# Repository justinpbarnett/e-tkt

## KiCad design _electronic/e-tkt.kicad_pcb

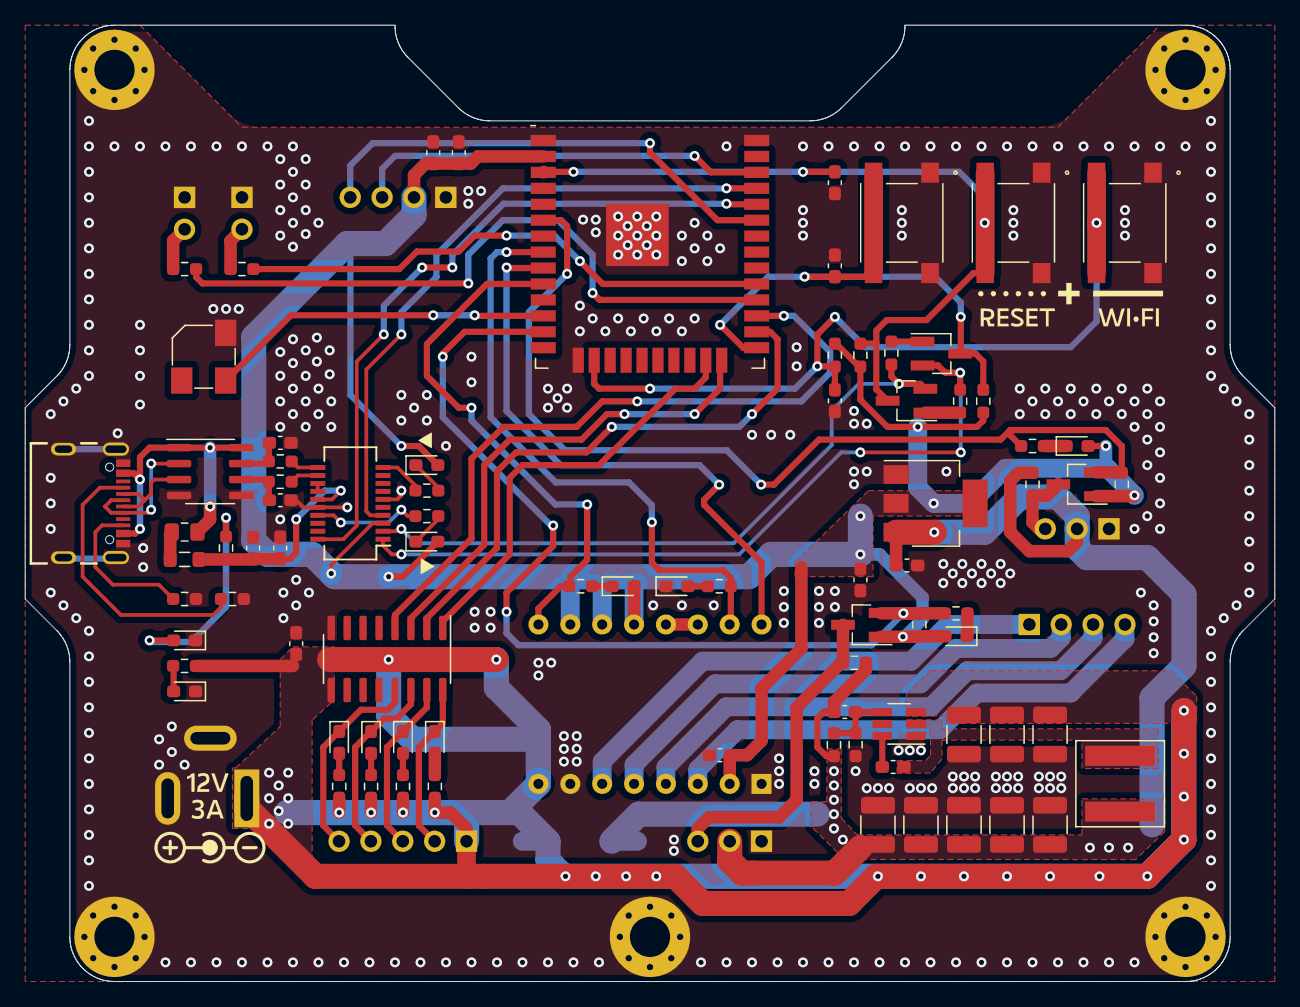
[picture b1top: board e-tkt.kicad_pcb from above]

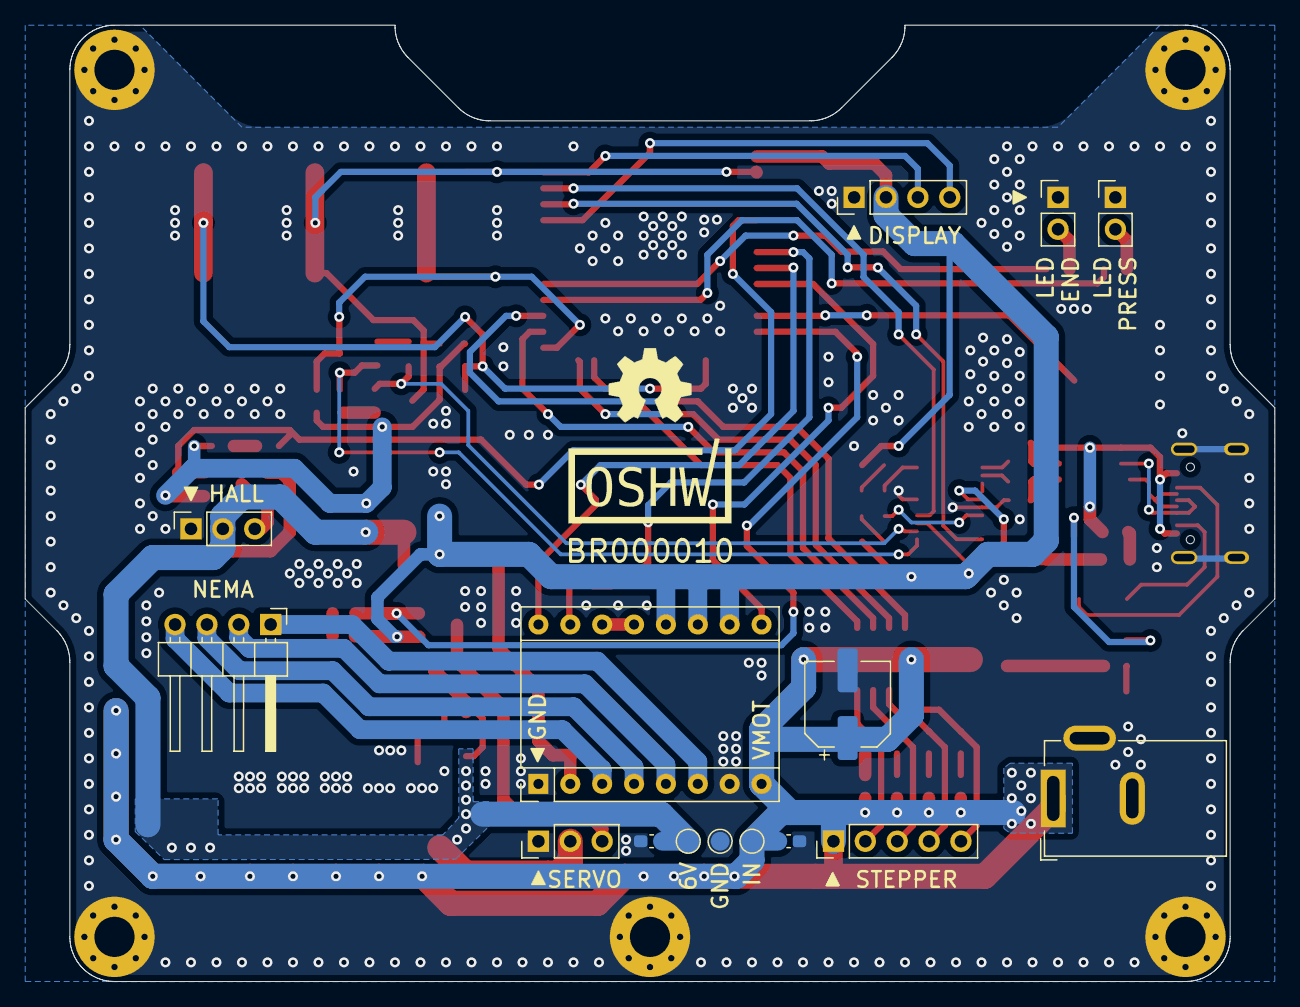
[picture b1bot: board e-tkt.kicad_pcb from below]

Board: 4 copper layers, 99.6 x 76.2 mm, 102 parts (15 on the bottom side), 69 nets.

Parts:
A_NEMA1: 8+8 pin; Pololu_Breakout-16_15.2x20.3mm
C_ENA1: 0.1uF 50V; C_0603_1608Metric_Pad1.08x0.95mm_HandSolder
C_MCU1: 0.1uF 50V; C_0603_1608Metric_Pad1.08x0.95mm_HandSolder
C_MCU2: 22uF 12V 1mOhm; C_0603_1608Metric_Pad1.08x0.95mm_HandSolder
C_NEMA1: 100uF 25V; CP_Elec_6.3x7.7
C_NEMA2: 10uF 12V 5mOhm; C_0603_1608Metric_Pad1.08x0.95mm_HandSolder
C_POW1: 10uF 12V 5mOhm; C_0603_1608Metric_Pad1.08x0.95mm_HandSolder
C_POW2: 22uF 12V 1mOhm; C_0603_1608Metric_Pad1.08x0.95mm_HandSolder
C_POW_6V_FF1: 82pF 100V; C_0603_1608Metric_Pad1.08x0.95mm_HandSolder
C_POW_BST1, C_POW_BST3: 0.1uF 50V; C_0603_1608Metric_Pad1.08x0.95mm_HandSolder
C_POW_BST2: 0.33uF 50V; C_0603_1608Metric_Pad1.08x0.95mm_HandSolder
C_POW_IN1, C_POW_IN2, C_POW_IN3: 10uF 25V; C_1210_3225Metric_Pad1.33x2.70mm_HandSolder
C_POW_OUT1, C_POW_OUT2, C_POW_OUT3, C_POW_OUT4, C_POW_OUT5: 22uF 25V; C_1210_3225Metric_Pad1.33x2.70mm_HandSolder
C_RST1: 0.1uF 50V; C_0603_1608Metric_Pad1.08x0.95mm_HandSolder
C_SER2, C_SER3: 47pF 5V; C_0603_1608Metric_Pad1.08x0.95mm_HandSolder
C_SER4: 0.1uF 50V; C_0603_1608Metric_Pad1.08x0.95mm_HandSolder
C_SER5: 10uF 12V 5mOhm; C_0603_1608Metric_Pad1.08x0.95mm_HandSolder
C_STP1: 10uF 12V 5mOhm; C_0603_1608Metric_Pad1.08x0.95mm_HandSolder
C_WIFI1: 0.1uF 50V; C_0603_1608Metric_Pad1.08x0.95mm_HandSolder
D_HALL1: LED white; LED_0603_1608Metric_Pad1.05x0.95mm_HandSolder
D_NEMA1, D_NEMA2: LED white; LED_0603_1608Metric_Pad1.05x0.95mm_HandSolder
D_POW2: LED white; LED_0603_1608Metric_Pad1.05x0.95mm_HandSolder
D_RX1: LED white; LED_0603_1608Metric_Pad1.05x0.95mm_HandSolder
D_SERVO1: LED white; LED_0603_1608Metric_Pad1.05x0.95mm_HandSolder
D_STP1, D_STP2, D_STP3, D_STP4: LED white; LED_0603_1608Metric_Pad1.05x0.95mm_HandSolder
D_TX1: LED white; LED_0603_1608Metric_Pad1.05x0.95mm_HandSolder
D_USB1: LED white; LED_0603_1608Metric_Pad1.05x0.95mm_HandSolder
FB_USB1: 40 Ohms @ 100 MHz 1 Power; L_0805_2012Metric_Pad1.05x1.20mm_HandSolder
F_USB1: 6V 750mA; Fuse_0805_2012Metric_Pad1.15x1.40mm_HandSolder
H1, H2, H3, H4, H6: M3; MountingHole_3.2mm_M3_Pad_Via
J_28byj-48-12v_1: Conn_01x05_Male; PinHeader_1x05_P2.54mm_Vertical
J_B_6v_1, J_B_12v_1: TestPoint; TestPoint_Pad_D1.5mm
J_B_GND_1: TestPoint; TestPoint_Pad_D1.5mm
J_HALL1: Conn_01x03_Female; PinSocket_1x03_P2.54mm_Vertical
J_LEDE1: Conn_01x02_Male; PinHeader_1x02_P2.54mm_Vertical
J_LEDP1: Conn_01x02_Male; PinHeader_1x02_P2.54mm_Vertical
J_NEMA1: Conn_01x04_Male; PinHeader_1x04_P2.54mm_Horizontal
J_OLED1: Conn_01x04_Male; PinHeader_1x04_P2.54mm_Vertical
J_POW1: Barrel_Jack_Switch; BarrelJack_GCT_DCJ200-10-A_Horizontal
J_SERVO1: Conn_01x03_Male; PinHeader_1x03_P2.54mm_Vertical
J_USB1: USB4105-GF-A; GCT_USB4105-GF-A
L1: SRP6060FA-100M; SRP6060FA-4R7M
LS1: CSS-0575A-SMT; CUI_CSS-0575A-SMT
Q_AUTO1, Q_AUTO2: SS8050; SOT-23_Handsoldering
Q_HALL1: BSS138LT3G; SOT-23_Handsoldering
Q_SERVO1: BSS138LT3G; SOT-23_Handsoldering
R_AUTO1, R_AUTO2: 10K (5%); R_0603_1608Metric_Pad0.98x0.95mm_HandSolder
R_ENA1: 10K (5%); R_0603_1608Metric_Pad0.98x0.95mm_HandSolder
R_HALL1, R_HALL2: 10K (5%); R_0603_1608Metric_Pad0.98x0.95mm_HandSolder
R_HALL3: 27R; R_0603_1608Metric_Pad0.98x0.95mm_HandSolder
R_LEDE1: 27R; R_0603_1608Metric_Pad0.98x0.95mm_HandSolder
R_LEDP1: 27R; R_0603_1608Metric_Pad0.98x0.95mm_HandSolder
R_NEMA1, R_NEMA2: 27R; R_0603_1608Metric_Pad0.98x0.95mm_HandSolder
R_POW6: 430R; R_0603_1608Metric_Pad0.98x0.95mm_HandSolder
R_POW_FBT1: 100K; R_0603_1608Metric_Pad0.98x0.95mm_HandSolder
R_POW_FFB1: 11K; R_0603_1608Metric_Pad0.98x0.95mm_HandSolder
R_RST1: 10K (5%); R_0603_1608Metric_Pad0.98x0.95mm_HandSolder
R_RX1: 27R; R_0603_1608Metric_Pad0.98x0.95mm_HandSolder
R_SER1, R_SER2: 27R; R_0603_1608Metric_Pad0.98x0.95mm_HandSolder
R_SERVO1, R_SERVO2: 10K (5%); R_0603_1608Metric_Pad0.98x0.95mm_HandSolder
R_SERVO3: 27R; R_0603_1608Metric_Pad0.98x0.95mm_HandSolder
R_STP1, R_STP2, R_STP3, R_STP4: 430R; R_0603_1608Metric_Pad0.98x0.95mm_HandSolder
R_TX1: 27R; R_0603_1608Metric_Pad0.98x0.95mm_HandSolder
R_USB1, R_USB2: 5.1K (10%); R_0603_1608Metric_Pad0.98x0.95mm_HandSolder
R_USB3: 100R; R_0603_1608Metric_Pad0.98x0.95mm_HandSolder
R_WIFI1: 10K(5%); R_0603_1608Metric_Pad0.98x0.95mm_HandSolder
SW_ENA1: B3FS-1000
SW_RST1: B3FS-1000
SW_WIFI1: B3FS-1000
U_MCU1: ESP32-WROOM-32
U_POW1: SOT-23-6_Handsoldering
U_POW2: AZ1117CH-3.3TRG1; SOT-223
U_SER1: FT231XS-R; SSOP-20_3.9x8.7mm_P0.635mm
U_STP1: ULN2003; SOIC-16_3.9x9.9mm_P1.27mm
U_USB1: USB6B1; SOIC-8_3.9x4.9mm_P1.27mm

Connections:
+3.3V: A_NEMA1.2 (VDD), A_NEMA1.10 (MS1), A_NEMA1.11 (MS2), A_NEMA1.12 (MS3), C_MCU1.1, C_MCU2.2, C_NEMA2.2, C_POW2.1, D_HALL1.2 (A), D_NEMA1.2 (A), D_RX1.2 (A), D_SERVO1.2 (A), D_TX1.2 (A), J_OLED1.2, Q_HALL1.1 (G), Q_SERVO1.1 (G), R_ENA1.2, R_HALL2.2, R_RST1.1, R_SERVO2.2, R_WIFI1.2, U_MCU1.2 (VDD), U_POW2.2 (OUT), U_POW2.4 (VOUT), U_SER1.3 (VCCIO)
+6V: C_POW1.1, C_POW_6V_FF1.1, C_POW_BST3.1, C_POW_OUT1.1, C_POW_OUT2.1, C_POW_OUT3.1, C_POW_OUT4.1, C_POW_OUT5.1, J_B_6v_1.1, J_HALL1.2, J_SERVO1.2, L1.2, R_HALL1.2, R_POW_FBT1.2, R_SERVO1.2, U_POW2.3 (IN)
+12V: A_NEMA1.8 (VMOT), C_NEMA1.1, C_POW_BST2.2, C_POW_IN1.1, C_POW_IN2.1, C_POW_IN3.1, C_STP1.2, J_28byj-48-12v_1.1, J_B_12v_1.1, J_POW1.1, R_POW6.1, R_STP1.1, R_STP2.1, R_STP3.1, R_STP4.1, U_POW1.3 (VIN), U_STP1.9 (COM)
/MCU/IO27 BUZZER OUT: LS1.1, U_MCU1.12 (IO27)
/USB-C 2.0/USBD1+: J_USB1.A6 (DP1), J_USB1.B6 (DP2), U_USB1.2 (I/O1)
/USB-C 2.0/USBD1-: J_USB1.A7 (DN1), J_USB1.B7 (DN2), U_USB1.3 (I/O2)
D+: C_SER3.2, R_SER2.2, U_USB1.7 (I/O1)
D-: C_SER2.2, R_SER1.2, U_USB1.6 (I/O2)
DTR: Q_AUTO2.2 (E), R_AUTO1.1, U_SER1.1 (~DTR)
EN: C_ENA1.2, Q_AUTO1.3 (C), R_ENA1.1, SW_ENA1.3, SW_ENA1.4, U_MCU1.3 (EN)
GNDREF: A_NEMA1.1 (GND), A_NEMA1.7 (GND), C_ENA1.1, C_MCU1.2, C_MCU2.1, C_NEMA1.2, C_NEMA2.1, C_POW1.2, C_POW2.2, C_POW_BST2.1, C_POW_BST3.2, C_POW_IN1.2, C_POW_IN2.2, C_POW_IN3.2, C_POW_OUT1.2, C_POW_OUT2.2, C_POW_OUT3.2, C_POW_OUT4.2, C_POW_OUT5.2, C_RST1.1, C_SER2.1, C_SER3.1, C_SER4.2, C_SER5.1, C_STP1.1, C_WIFI1.1, D_NEMA2.1 (K), D_POW2.1 (K), D_USB1.1 (K), H1.1, H2.1, H3.1, H4.1, H6.1, J_B_GND_1.1, J_HALL1.1, J_LEDE1.1, J_LEDP1.1, J_OLED1.1, J_POW1.2, J_POW1.3, J_SERVO1.1, J_USB1.A1_B12 (GND), J_USB1.B1_A12 (GND), J_USB1.S1 (SHELL_GND), J_USB1.S2 (SHELL_GND), J_USB1.S3 (SHELL_GND), J_USB1.S4 (SHELL_GND), LS1.2, R_POW_FFB1.1, R_USB1.1, R_USB2.1, SW_ENA1.1, SW_ENA1.2, SW_RST1.1, SW_RST1.2, SW_WIFI1.1, SW_WIFI1.2, U_MCU1.1 (GND), U_MCU1.15 (GND), U_MCU1.38 (GND), U_MCU1.39 (GND), U_POW1.1 (GND), U_POW2.1 (ADJ/GND), U_SER1.6 (GND), U_SER1.16 (GND), U_STP1.8 (GND), U_USB1.4 (GND), U_USB1.5 (GND)
HALL: J_HALL1.3, Q_HALL1.3 (D), R_HALL1.1
IO0 RESET: C_RST1.2, Q_AUTO2.3 (C), R_RST1.2, SW_RST1.3, SW_RST1.4, U_MCU1.25 (IO0)
IO1 TXD: U_MCU1.35 (TXD0/IO1), U_SER1.4 (RXD)
IO2 ULN 3: U_MCU1.24 (IO2), U_STP1.3 (I3)
IO3 RXD: U_MCU1.34 (RXD0/IO3), U_SER1.20 (TXD)
IO4 ULN 2: U_MCU1.26 (IO4), U_STP1.2 (I2)
IO5 LED END: R_LEDE1.1, U_MCU1.29 (IO5)
IO13 WIFI RST: C_WIFI1.2, R_WIFI1.1, SW_WIFI1.3, SW_WIFI1.4, U_MCU1.16 (IO13)
IO14 SERVO: Q_SERVO1.2 (S), R_SERVO2.1, R_SERVO3.1, U_MCU1.13 (IO14)
IO15 ULN 1: U_MCU1.23 (IO15), U_STP1.1 (I1)
IO16 ULN 4: U_MCU1.27 (IO16), U_STP1.4 (I4)
IO17 LED PRESS: R_LEDP1.1, U_MCU1.28 (IO17)
IO21 OLED SDA: J_OLED1.4, U_MCU1.33 (IO21)
IO22 OLED SCL: J_OLED1.3, U_MCU1.36 (IO22)
IO25 NEMA ENA: A_NEMA1.9 (~ENABLE), R_NEMA1.1, U_MCU1.10 (IO25)
IO32 NEMA STEP: A_NEMA1.15 (STEP), R_NEMA2.2, U_MCU1.8 (IO32)
IO33 NEMA DIR: A_NEMA1.16 (DIR), U_MCU1.9 (IO33)
IO34 HALL: Q_HALL1.2 (S), R_HALL2.1, R_HALL3.1, U_MCU1.6 (IO34)
unnamed: A_NEMA1.3 (1B), J_NEMA1.4
unnamed: A_NEMA1.4 (1A), J_NEMA1.3
unnamed: A_NEMA1.5 (2A), J_NEMA1.2
unnamed: A_NEMA1.6 (2B), J_NEMA1.1
unnamed: A_NEMA1.13 (~RESET), A_NEMA1.14 (~SLEEP)
unnamed: C_POW_6V_FF1.2, R_POW_FBT1.1, R_POW_FFB1.2, U_POW1.4 (FB)
unnamed: C_POW_BST1.1, U_POW1.6 (BOOT)
unnamed: C_POW_BST1.2, L1.1, U_POW1.2 (SW)
unnamed: D_NEMA2.2 (A), R_NEMA2.1
unnamed: D_POW2.2 (A), R_POW6.2
unnamed: D_RX1.1 (K), R_RX1.1
unnamed: D_SERVO1.1 (K), R_SERVO3.2
unnamed: D_STP1.1 (K), J_28byj-48-12v_1.2, U_STP1.16 (O1)
unnamed: D_STP1.2 (A), R_STP1.2
unnamed: D_STP2.1 (K), J_28byj-48-12v_1.3, U_STP1.15 (O2)
unnamed: D_STP2.2 (A), R_STP2.2
unnamed: D_STP3.1 (K), J_28byj-48-12v_1.4, U_STP1.14 (O3)
unnamed: D_STP3.2 (A), R_STP3.2
unnamed: D_STP4.1 (K), J_28byj-48-12v_1.5, U_STP1.13 (O4)
unnamed: D_STP4.2 (A), R_STP4.2
unnamed: D_TX1.1 (K), R_TX1.1
unnamed: D_USB1.2 (A), R_USB3.1
unnamed: FB_USB1.1, F_USB1.2
unnamed: F_USB1.1, J_USB1.A4_B9 (VBUS), J_USB1.B4_A9 (VBUS), U_USB1.1 (VBUS), U_USB1.8 (VBUS)
unnamed: J_LEDE1.2, R_LEDE1.2
unnamed: J_LEDP1.2, R_LEDP1.2
unnamed: J_USB1.A5 (CC1), R_USB1.2
unnamed: J_USB1.B5 (CC2), R_USB2.2
unnamed: Q_AUTO1.1 (B), R_AUTO1.2
unnamed: Q_AUTO2.1 (B), R_AUTO2.2
unnamed: D_HALL1.1 (K), R_HALL3.2
unnamed: D_NEMA1.1 (K), R_NEMA1.2
unnamed: R_RX1.2, U_SER1.17 (CBUS1)
unnamed: R_SER1.1, U_SER1.12 (USBDM)
unnamed: R_SER2.1, U_SER1.11 (USBDP)
unnamed: R_TX1.2, U_SER1.10 (CBUS2)
unnamed: U_SER1.13 (3V3OUT), U_SER1.14 (~RESET)
RTS: Q_AUTO1.2 (E), R_AUTO2.1, U_SER1.2 (~RTS)
SERVO: J_SERVO1.3, Q_SERVO1.3 (D), R_SERVO1.1
VBUS: C_SER4.1, C_SER5.2, FB_USB1.2, R_USB3.2, U_SER1.15 (VCC)

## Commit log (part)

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2022-10-13 new 3d source file
2022-10-14 buzzer pin on new pcb
2022-10-16 removed led end on testing
2022-10-17 Rename 01_nema_stepper.md to 01_harnesses.md
2022-10-17 Rename 06_display.md to 06_feed.md
2022-10-17 Rename 07_top.md to 07_daisywheel.md
2022-10-17 Rename 01_harnesses.md to 00_harnesses.md
2022-10-17 Rename 04_chassis.md to 03_chassis.md
2022-10-17 Create 08_
2022-10-17 Rename 08_ to 08_feeder
2022-10-17 Rename 08_feeder to 08_feeder.md
2022-10-17 fixed wrong hall header on pcb
2022-10-18 fixed hall header on pcb
2022-10-18 removed old electronic files
2023-01-01 Use lowercase for the font file name as the webserver expects
2023-01-11 Make some hardware parameters configurable
2023-01-14 Move UI state handling into the webserver
2023-01-15 Undo accidental change to default serial settings
2023-02-08 separate file for optional config (hall/direction)
2023-02-08 improved code visibility for opt config
2023-02-08 configured gitignore for optional config
2023-02-08 fixed 99% progress when beginning printing
2023-02-17 Note the prevChar is changed during homing
    Otherwise the printer can print the wrong character at the start of a print
2023-02-17 Make input elements selectable
    This is necessary to make UI elements work on safari mobile. Other browsers are suspiciously unaffected despite how that CSS is supposed to work.
2023-03-12 Support UTF8 and scroll for longer label text
2023-03-20 fixes 'char' to 'const char*' convertion error
2023-03-20 form button labels not selectable anymore
2023-03-30 Make settings use the correct task endpoint
2023-03-30 Add a server that simulates a physical E-TKT
2023-04-12 Update bom.md
    Added proper spec names for fasteners and replaced 2 rotted links with generic search links
2023-04-13 Update bom.md
    Replaced rotted links with new ones or search links (the servo is currently only available as multiple).
    Also added an example for the power brick.
2023-04-13 Add PCB specs to electronics.md
    Add PCB specs for people that don't know what to enter when ordering PCBs.
2023-04-16 Correct OLED control chip designation
    Accidentally added wrong chip designation in previous commit.
2023-04-19 add separated 3D STEP files, by layer
2023-04-19 updated step files, m3x16 side screws
2023-04-19 updated stl files, m3x16 side screws
2023-04-19 remove backup files
2023-04-20 added first version of custom pressWheel
2023-04-21 scrolling text input
2023-04-24 improved custom wheel test
2023-04-24 adjusted custom wheel parameters
2023-04-24 tips beside text input when scrolled mid way
2023-04-24 cross-browser scrollbars and some QOL improvements
    I've added a bunch of logic to handle different browser eccentricities:
    - I've verified that iOS never displays a scrollbar, which I suppose iOS users are comfortable with.
    - I've added lots of fancy CSS selectors to make the scrollbars as visually consistent on firefox desktop and mobile as possible. This is accomplished by adding a ```position: sticky``` element insid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
    I also made a number of other quality-of-life
2023-04-25 Remove sources of layout height shifting
2023-04-25 added a section cut option to help with tuning
2023-04-25 closed the small gaps at bottom disc center
2023-04-25 embHght represents the char height again
2023-04-25 introduced option to show the positives in the topwheel to better see spacing spacings are now selectable for XY and Z separately
2023-04-25 added option to render labels to the top disc
2023-04-25 started experimenting with fonts
2023-04-25 created module for 16segment display
2023-04-25 preparations for presets
2023-04-25 Update pressWheel.scad
    user can now select to create a 16-segment inspired wheel. Letters and numbers needs to be combined by multiple presses without feeding the tape.
2023-04-25 limits the number of musical tones to 16
2023-04-25 limits the input characters to approx. 1 meter
2023-04-25 jumping to text scroll start and end
2023-04-28 Speed up the song for long labels
2023-04-28 Add hover to scroll tips, and hide when printing
2023-04-29 Configure optional OTA updates
2023-04-29 Revert some accidentally submitted #define changes
2023-04-29 Sync print progress across browser sessions
2023-05-02 Break out firmware into multiple classes.
2023-05-03 Fix progress reporting (webapp and firmware)
2023-05-03 Properly handle printer busy error
2023-05-03 Add monitoring for uptime and memory
2023-05-03 rename from Carousel to DaisyWheel
2023-05-03 standardized some header descriptions
2023-05-04 fixes the LEDs behavior
2023-05-04 disables autofill keyboard bar on input

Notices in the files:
parts and their libraries:
Copyright 2021 Accelerated Designs. All rights reserved.
